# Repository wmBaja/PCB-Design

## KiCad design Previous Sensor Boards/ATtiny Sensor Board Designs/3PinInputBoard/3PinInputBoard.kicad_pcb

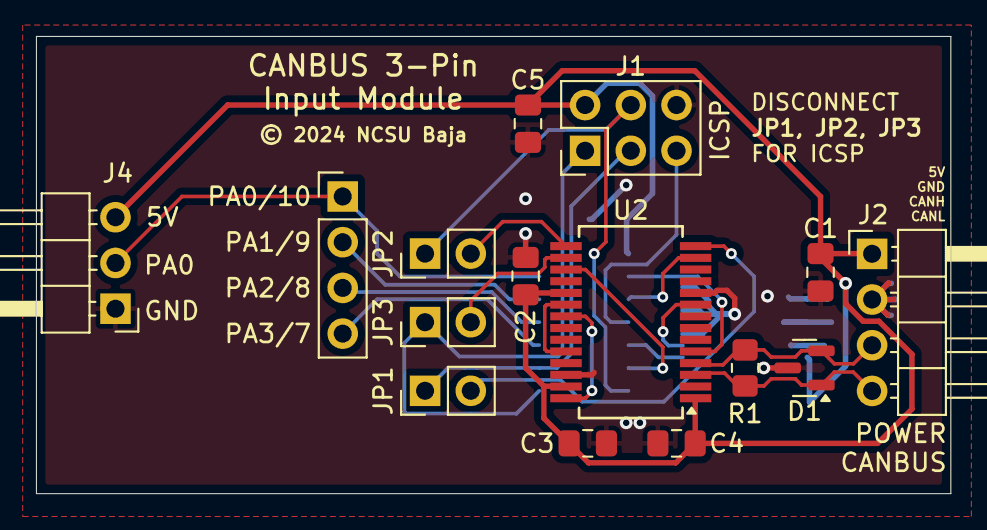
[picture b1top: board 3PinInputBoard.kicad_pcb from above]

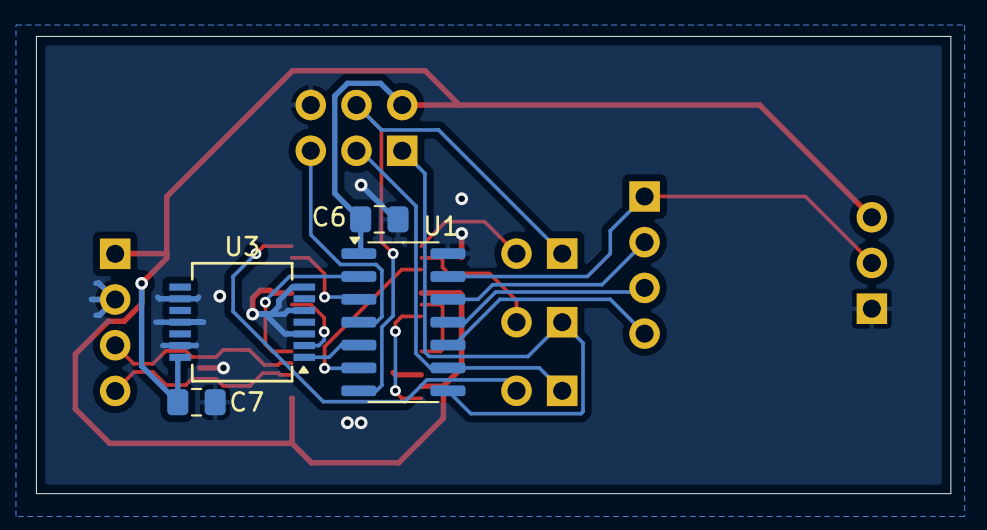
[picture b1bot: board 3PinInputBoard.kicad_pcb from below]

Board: 2 copper layers, 50.8 x 25.4 mm, 19 parts (4 on the bottom side), 22 nets.

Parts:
C1, C2, C3, C4, C5, C6, C7: 0.1u; C_0805_2012Metric_Pad1.18x1.45mm_HandSolder
D1: PESD5V0S2BT; SOT-23
J1: ICSP; PinHeader_2x03_P2.54mm_Vertical
J2: POWER/CAN; PinHeader_1x04_P2.54mm_Horizontal
J3: Conn_01x04; PinHeader_1x04_P2.54mm_Vertical
J4: Conn_01x03; PinHeader_1x03_P2.54mm_Horizontal
JP1, JP2, JP3: Jumper_2_Bridged; PinHeader_1x02_P2.54mm_Vertical
R1: 120; R_0805_2012Metric_Pad1.20x1.40mm_HandSolder
U1: ATtiny841-SS; SOIC-14_3.9x8.7mm_P1.27mm
U2: MCP25625-x-SS; SSOP-28_5.3x10.2mm_P0.65mm
U3: 74HC04; SSOP-14_5.3x6.2mm_P0.65mm

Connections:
+5V: C1.2, C2.2, C3.1, C4.1, C5.1, C6.2, C7.1, J1.2, J2.1, J4.3, U1.1 (VCC), U2.1 (VIO), U2.19 (VDD), U2.27 (VDDA), U3.14 (VCC)
/CAN_N: D1.1, J2.4, R1.2, U2.3 (CANL)
/CAN_P: D1.2, J2.3, R1.1, U2.4 (CANH)
/MISO: J1.1, JP3.1 (A), U1.8 (PA5)
/MOSI: J1.4, JP2.1 (A), U1.7 (PA6)
/SCK: J1.3, JP1.1 (A), U1.9 (PA4)
/STBY: U1.2 (XTAL1/PB0), U2.5 (STBY)
/SYSCLK: U1.5 (PB2), U3.1
/USER0: J3.1, J4.2, U1.13 (AREF/PA0)
/USER1: J3.2, U1.12 (PA1)
/USER2: J3.3, U1.11 (PA2)
/USER3: J3.4, U1.10 (PA3)
/~RESET: J1.5, U1.4 (~RESET/PB3)
/~SS: U1.6 (PA7), U2.17 (~CS)
GND: C1.1, C2.1, C3.2, C4.2, C5.2, C6.1, C7.2, D1.3, J1.6, J2.2, J4.1, U1.14 (GND), U2.10 (GND), U2.26 (VSS), U3.3, U3.5, U3.7 (GND), U3.9, U3.11, U3.13
unnamed: JP1.2 (B), U2.14 (SCK)
unnamed: JP2.2 (B), U2.15 (SI)
unnamed: JP3.2 (B), U2.16 (SO)
unnamed: U1.3 (XTAL2/PB1), U2.13 (~INT)
unnamed: U2.9 (OSC1), U3.2
unnamed: U2.21 (RxCAN), U2.28 (RXD)
unnamed: U2.20 (TxCAN), U2.24 (TXD)

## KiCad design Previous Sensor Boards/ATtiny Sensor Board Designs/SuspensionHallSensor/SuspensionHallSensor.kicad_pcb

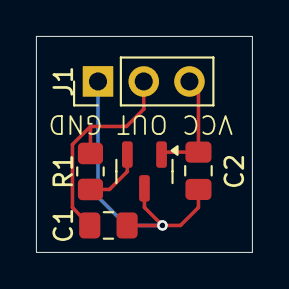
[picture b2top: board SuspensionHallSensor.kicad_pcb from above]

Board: 2 copper layers, 12.0 x 12.0 mm, 5 parts (0 on the bottom side), 4 nets.

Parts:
C1, C2: C_Small; C_0805_2012Metric_Pad1.18x1.45mm_HandSolder
J1: Conn_01x03_Pin; PinHeader_1x03_P2.54mm_Vertical
R1: R_Small; R_0805_2012Metric_Pad1.20x1.40mm_HandSolder
U1: DRV5055A1xDBZxQ1; SOT-23

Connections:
+5V: C2.1, J1.3, U1.1 (VCC)
GND: C1.2, C2.2, J1.1, U1.3 (GND)
unnamed: C1.1, J1.2, R1.2
unnamed: R1.1, U1.2 (OUT)

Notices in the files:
Previous Sensor Boards/ATtiny Sensor Board Designs/3PinInputBoard/3PinInputBoard.kicad_pcb:
© 2024 NCSU Baja
